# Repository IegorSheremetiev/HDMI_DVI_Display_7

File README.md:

### HDMI/DVI to LVDS(OLDI) Converter
These days we may find many electronic devices what are to old already or where the "white smoke" gone.
But could be that the display module is still alive!
Excatly this story started when my old and really weak netbook Acer A-150 just stopped working. There is no sense to try to restore it. Howevere there are several interesting modules inside. An I inspired to do something intersting with that parts.

First of all the idea of the current project is to realize its display module as the second tiny (7") disaply for the local PC.
Or, to get portable display for headless PCs. Time to time even for these machines the display is requried.
And later I found in my "almost trash boxes" the old tablet where HW is pretty old but the display and the touchscreen are really fine. Bu this is another story

## System definition and key components
As the input signal I chose TMDS based signals: DVI and HDMI. IN almost all cases these two standards are similar. HDMI has bonuses as it may include audio stream. ANd this idea I would like to realize. However market checks showed the lack of components with HDMI Audio support in stock. Nevertheless, if the HDMI doesn't inlcude Audio Stream DVI and HDMI are fully compatible.

Analog Interface (D-Sub) is fully feasible. However it old. Could be later but not now.

Key Components:
- [TFP401A](https://www.ti.com/product/TFP401A) - TMDS to RGB24 decoder; translate DV/HDMI digital signals to paraller RGB 8:8:8 interface, the device has ODD and EVEN outputs what gives to it ability to handle high resolutions
- [SN65LVDS93A](https://www.ti.com/product/SN65LVDS93A) - RGB24 to LVDS converter; serialize RGB signals into the LVDS interface (or OpenLDI) interface; different configurations of connections gives the possibility to use different color resolution of displays RGB12/RGB18/RGB24
- [TPS54286 or TPS54283](https://www.ti.com/lit/gpn/tps54283) - Dual DC-DC Converter for the system;
  - 3V3 as the main power supply for the system
  - 5V as the power supply for the backlight
- [AUO B089AW01-V1](https://datasheetspdf.com/pdf-file/1304972/AUO/B089AW01-V1/1) - the display module used in my broken netbook

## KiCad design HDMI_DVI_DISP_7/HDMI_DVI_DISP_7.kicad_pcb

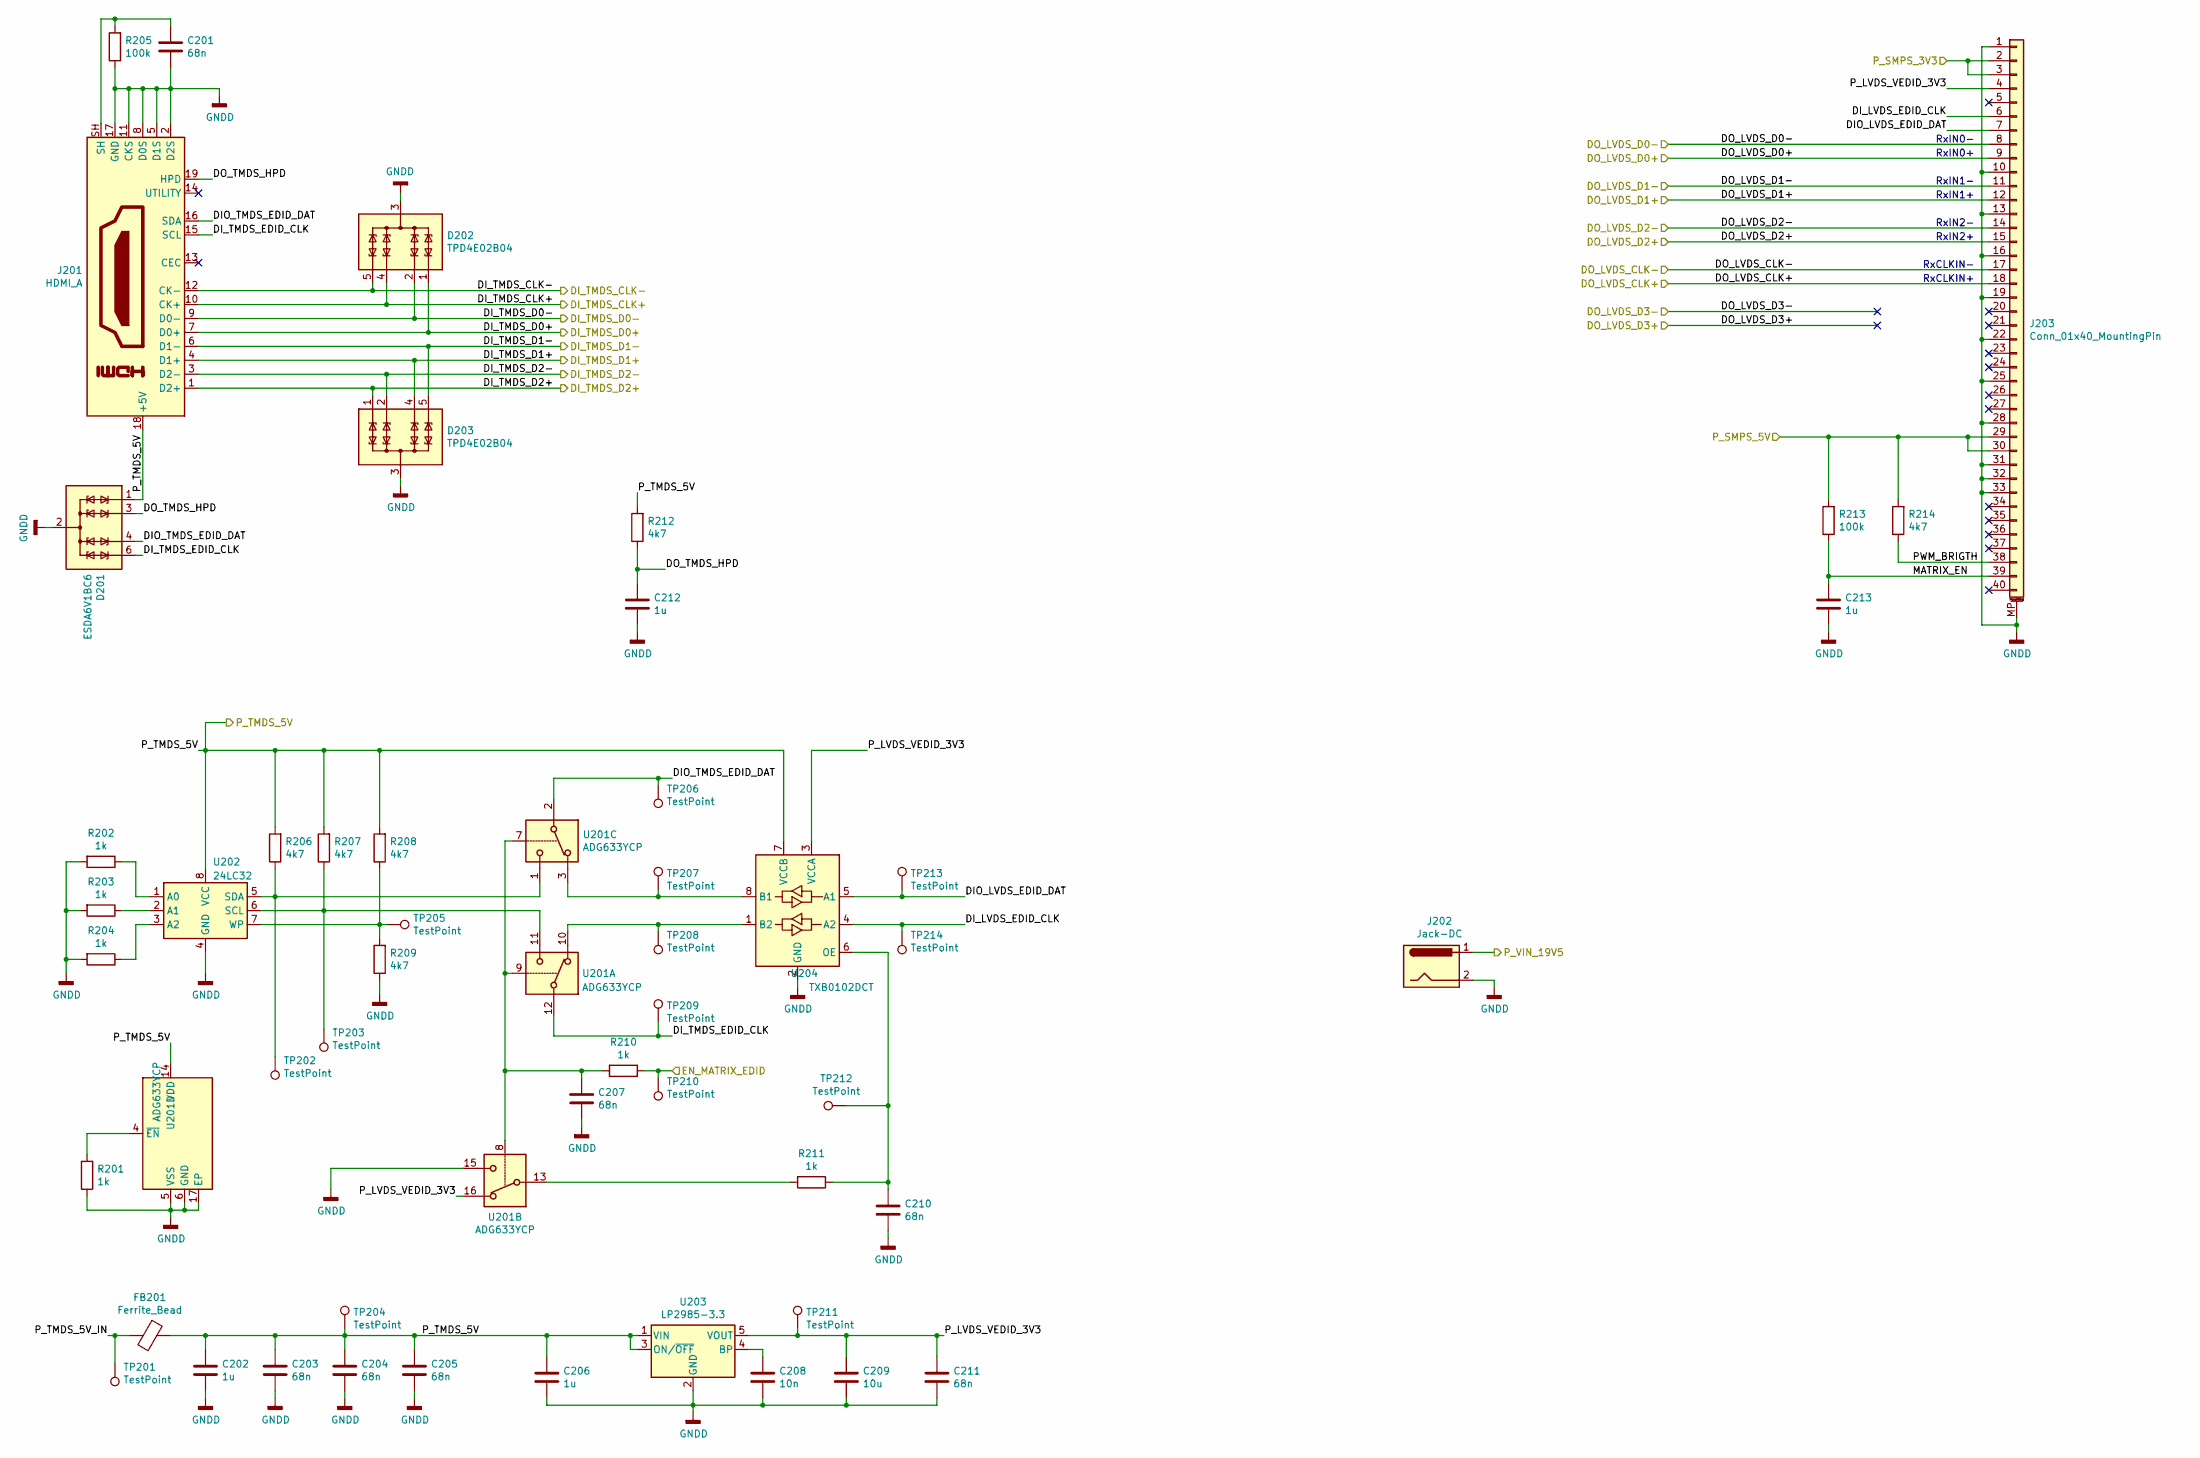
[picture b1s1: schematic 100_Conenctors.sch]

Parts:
C201, C203, C204, C205, C207, C210, C211: 68n; C_0402_1005Metric
C202, C206: 1u; C_0603_1608Metric
C208: 10n; C_0402_1005Metric
C209: 10u; C_0805_2012Metric
C212, C213: 1u; C_0402_1005Metric
D201: ESDA6V1BC6; SOT-23-6
D202, D203: TPD4E02B04; USON-10_-_1mm_x_2.5mm_x_0.55mm
FB201: Ferrite_Bead; L_0603_1608Metric
J201: HDMI_A; HDMI_A_19p_0.5mm
J202: Jack-DC; PinHeader_1x02_P1.27mm_Horizontal
J203: Conn_01x40_MountingPin; Hirose_FH12-40S-0.5SH_1x40-1MP_P0.50mm_Horizontal
R201, R202, R203, R204, R210, R211: 1k; R_0402_1005Metric
R205, R213: 100k; R_0402_1005Metric
R206, R207, R208, R209, R212, R214: 4k7; R_0402_1005Metric
TP201, TP202, TP203, TP204, TP205, TP206, TP207, TP208, TP209, TP210, TP211, TP212, TP213, TP214: TestPoint; TestPoint_Pad_D1.0mm
U201: ADG633YCP; LFCSP-16-1EP_4x4mm_P0.65mm_EP2.1x2.1mm
U202: 24LC32; SOIC-8_3.9x4.9mm_P1.27mm
U203: LP2985-3.3; SOT-23-5
U204: TXB0102DCT; TSSOP-8_3x3mm_P0.65mm

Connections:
/100_Conenctors/DIO_LVDS_EDID_DAT: J203.7, TP213.1, U204.5 (A1)
/100_Conenctors/DIO_TMDS_EDID_DAT: D201.4 (TVS3), J201.16 (SDA), TP206.1, U201.2
/100_Conenctors/DI_LVDS_EDID_CLK: J203.6, TP214.1, U204.4 (A2)
/100_Conenctors/DI_TMDS_CLK+: D202.4 (IO3), D202.7 (NC), J201.10 (CK+); also elsewhere on the board
/100_Conenctors/DI_TMDS_CLK-: D202.5 (IO4), D202.6 (NC), J201.12 (CK-); also elsewhere on the board
/100_Conenctors/DI_TMDS_D0+: D202.1 (IO1), D202.10 (NC), J201.7 (D0+); also elsewhere on the board
/100_Conenctors/DI_TMDS_D0-: D202.2 (IO2), D202.9 (NC), J201.9 (D0-); also elsewhere on the board
/100_Conenctors/DI_TMDS_D1+: D203.4 (IO3), D203.7 (NC), J201.4 (D1+); also elsewhere on the board
/100_Conenctors/DI_TMDS_D1-: D203.5 (IO4), D203.6 (NC), J201.6 (D1-); also elsewhere on the board
/100_Conenctors/DI_TMDS_D2+: D203.1 (IO1), D203.10 (NC), J201.1 (D2+); also elsewhere on the board
/100_Conenctors/DI_TMDS_D2-: D203.2 (IO2), D203.9 (NC), J201.3 (D2-); also elsewhere on the board
/100_Conenctors/DI_TMDS_EDID_CLK: D201.6 (TVS4), J201.15 (SCL), TP209.1, U201.12
/100_Conenctors/DO_LVDS_CLK+: J203.18; also elsewhere on the board
/100_Conenctors/DO_LVDS_CLK-: J203.17; also elsewhere on the board
/100_Conenctors/DO_LVDS_D0+: J203.9; also elsewhere on the board
/100_Conenctors/DO_LVDS_D0-: J203.8; also elsewhere on the board
/100_Conenctors/DO_LVDS_D1+: J203.12; also elsewhere on the board
/100_Conenctors/DO_LVDS_D1-: J203.11; also elsewhere on the board
/100_Conenctors/DO_LVDS_D2+: J203.15; also elsewhere on the board
/100_Conenctors/DO_LVDS_D2-: J203.14; also elsewhere on the board
/100_Conenctors/DO_TMDS_HPD: C212.1, D201.3 (TVS2), J201.19 (HPD), R212.1
/100_Conenctors/MATRIX_EN: C213.1, J203.39, R213.1
/100_Conenctors/PWM_BRIGTH: J203.38, R214.1
/100_Conenctors/P_LVDS_VEDID_3V3: C209.1, C211.1, J203.4, TP211.1, U201.16, U203.5 (VOUT), U204.3 (VCCA)
/100_Conenctors/P_TMDS_5V_IN: FB201.2, TP201.1
/900_Video_Links/DO_LVDS_EDID: R210.1, TP210.1; also elsewhere on the board
/P_SMPS_3V3: J203.2, J203.3; also elsewhere on the board
/P_SMPS_5V: J203.29, J203.30, R213.2, R214.2; also elsewhere on the board
/P_TMDS_5V: C202.1, C203.1, C204.1, C205.1, C206.1, D201.1 (TVS1), FB201.1, J201.18 (+5V), R206.2, R207.2, R208.2, R212.2, TP204.1, U201.14 (VDD), U202.8 (VCC), U203.1 (VIN), U203.3 (ON/~OFF~), U204.7 (VCCB); also elsewhere on the board
/P_VIN_19V5: J202.1; also elsewhere on the board
GNDD: C201.2, C202.2, C203.2, C204.2, C205.2, C206.2, C207.2, C208.2, C209.2, C210.2, C211.2, C212.2, C213.2, D201.2 (COM), D201.5 (COM), D202.3 (GND), D202.8 (GND), D203.3 (GND), D203.8 (GND), J201.2 (D2S), J201.5 (D1S), J201.8 (D0S), J201.11 (CKS), J201.17 (GND), J202.2, J203.1, J203.10, J203.13, J203.16, J203.19, J203.22, J203.25, J203.28, J203.31, J203.32, J203.33, J203.MP (MountPin), R201.1, R202.2, R203.2, R204.2, R205.1, R209.1, U201.5 (VSS), U201.6 (GND), U201.15, U201.17 (EP), U202.4 (GND), U203.2 (GND), U204.2 (GND); also elsewhere on the board
unnamed: C201.1, J201.SH, R205.2
unnamed: C207.1, R210.2, U201.7, U201.8, U201.9
unnamed: C208.1, U203.4 (BP)
unnamed: C210.1, R211.1, TP212.1, U204.6 (OE)
unnamed: R201.2, U201.4 (~EN)
unnamed: R202.1, U202.1 (A0)
unnamed: R203.1, U202.2 (A1)
unnamed: R204.1, U202.3 (A2)
unnamed: R206.1, TP202.1, U201.1, U202.5 (SDA)
unnamed: R207.1, TP203.1, U201.11, U202.6 (SCL)
unnamed: R208.1, R209.2, TP205.1, U202.7 (WP)
unnamed: R211.2, U201.13
unnamed: TP207.1, U201.3, U204.8 (B1)
unnamed: TP208.1, U201.10, U204.1 (B2)

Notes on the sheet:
RxIN0-
RxIN0+
RxIN1-
RxIN1+
RxIN2-
RxIN2+
RxCLKIN-
RxCLKIN+

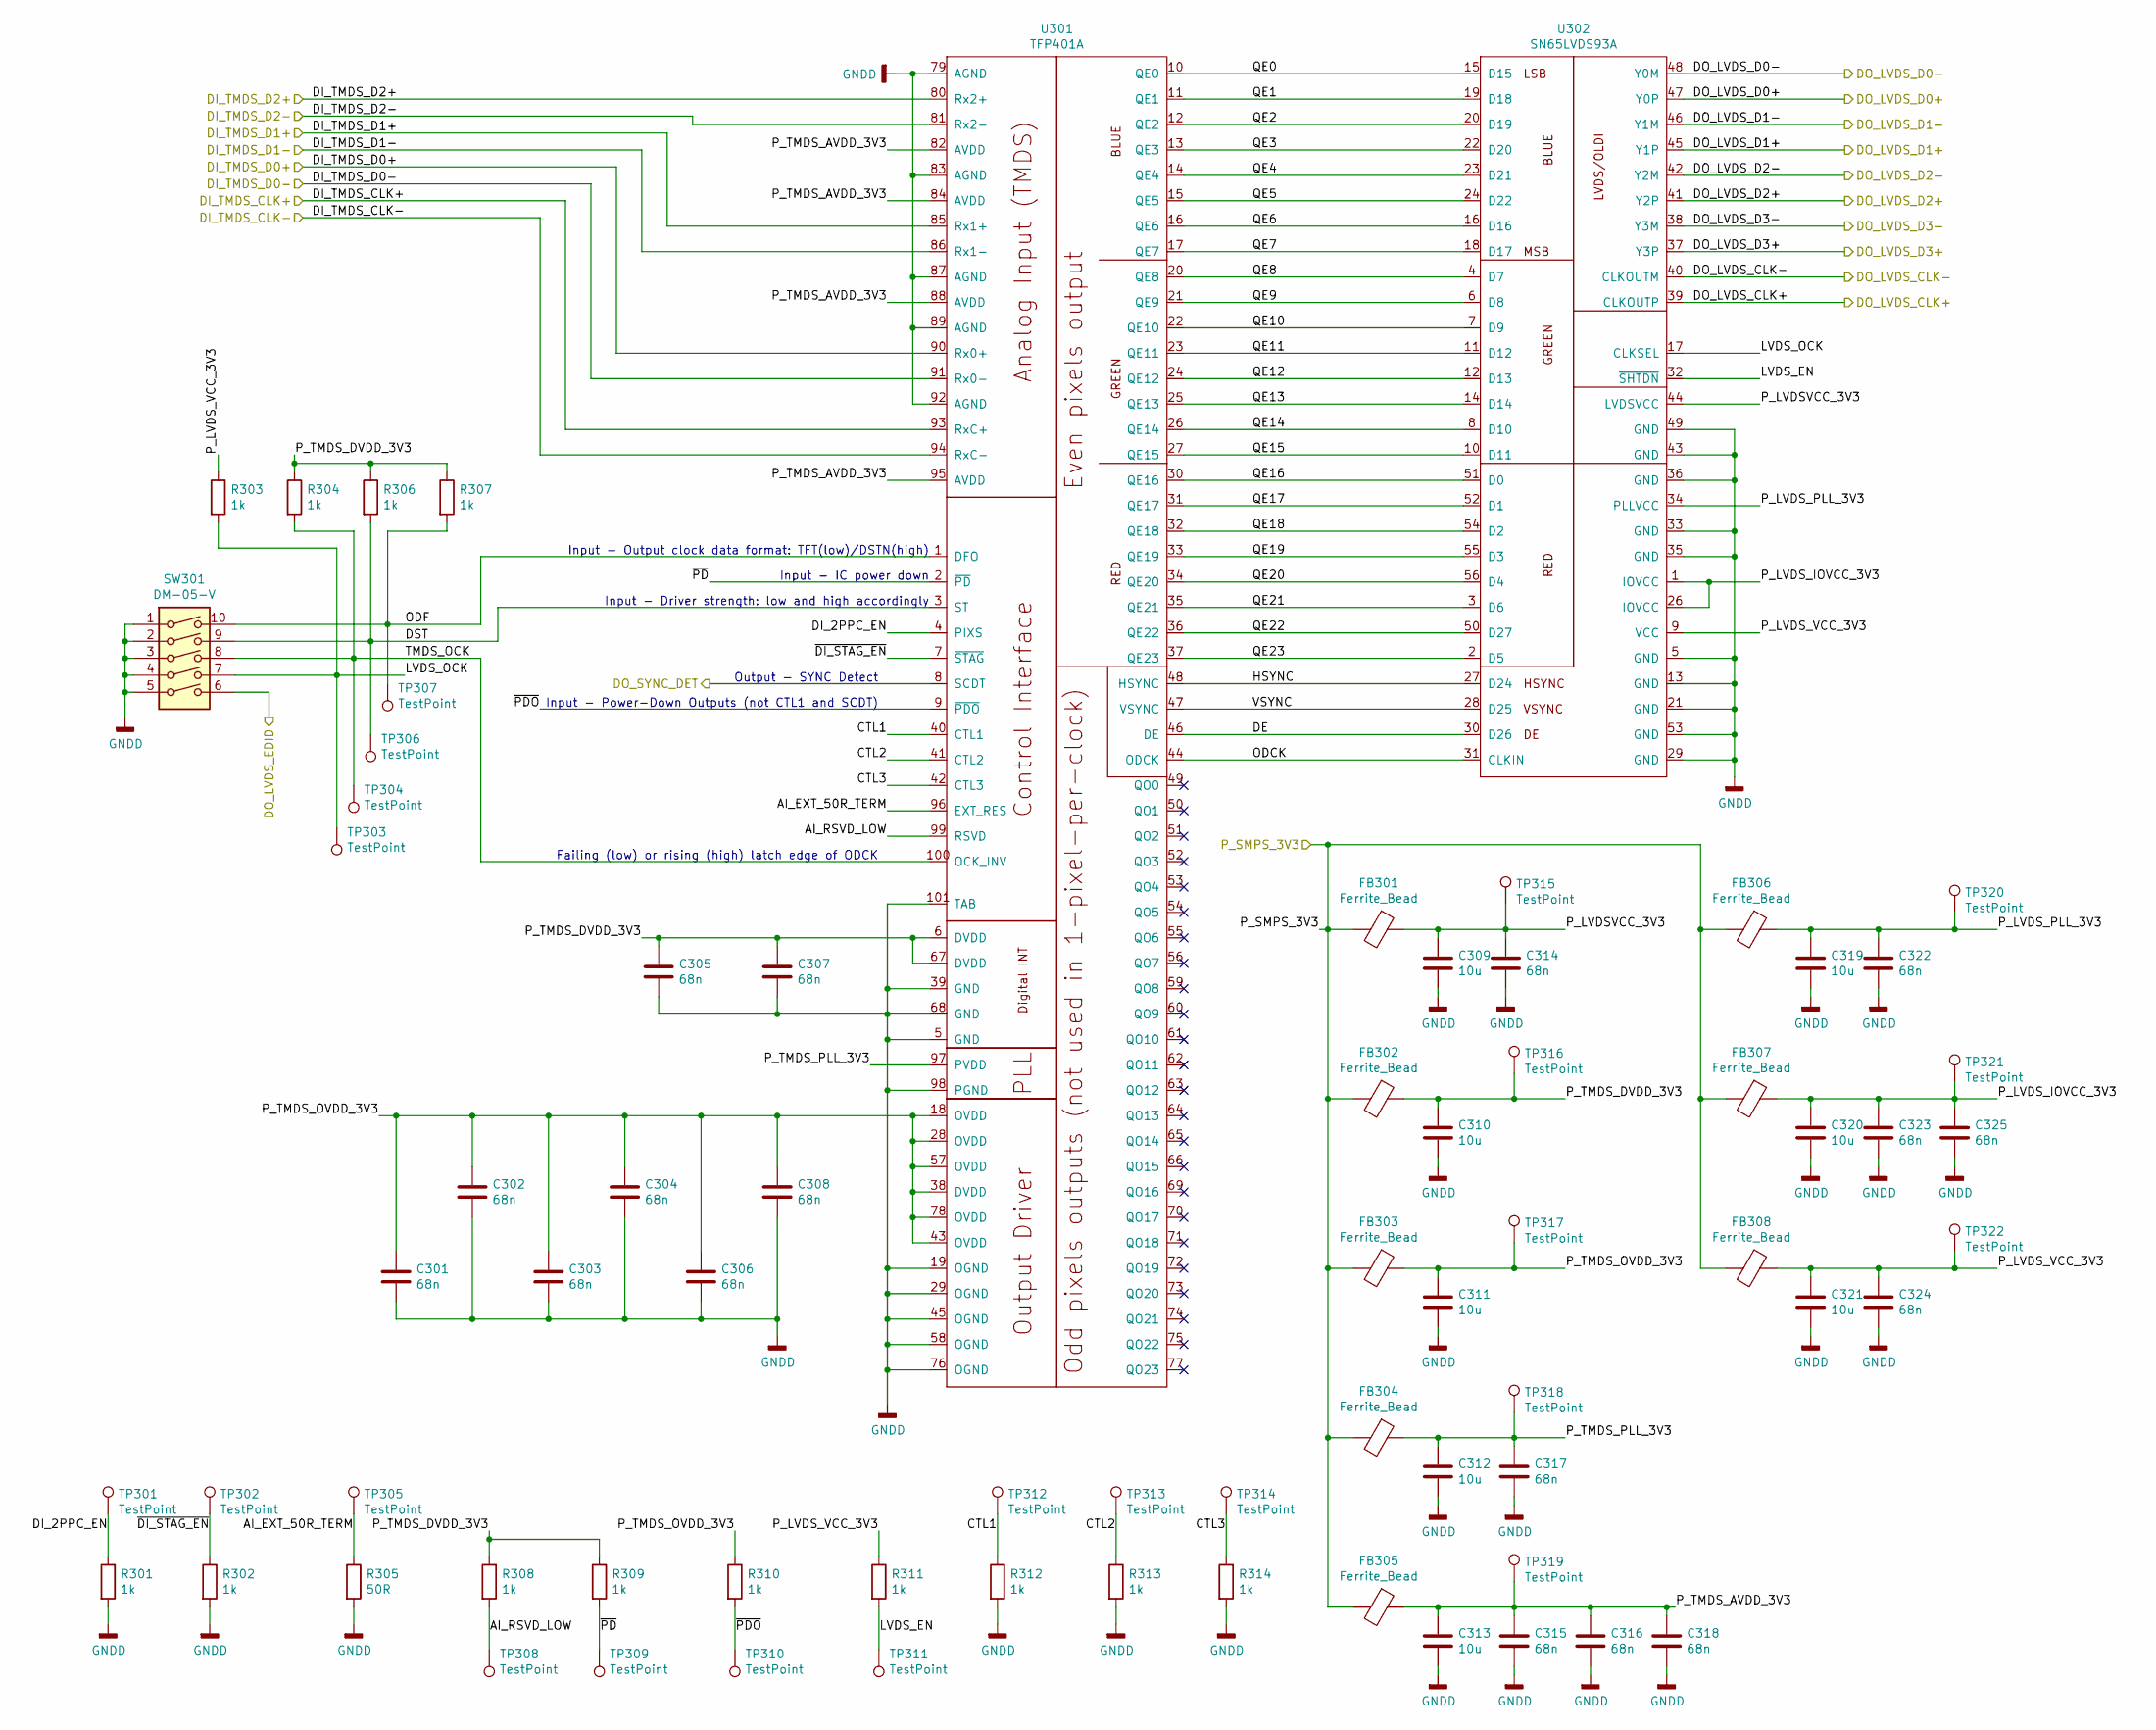
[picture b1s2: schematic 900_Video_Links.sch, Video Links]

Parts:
C301, C302, C303, C304, C305, C306, C307, C308, C314, C315, C316, C317, C318, C322, C323, C324, C325: 68n; C_0402_1005Metric
C309, C310, C311, C312, C313, C319, C320, C321: 10u; C_0805_2012Metric
FB301, FB302, FB303, FB304, FB305, FB306, FB307, FB308: Ferrite_Bead; L_0603_1608Metric
R301, R302, R303, R304, R306, R307, R308, R309, R310, R311, R312, R313, R314: 1k; R_0402_1005Metric
R305: 50R; R_0402_1005Metric
SW301: DM-05-V; SOIC-10-DM-05
TP301, TP302, TP303, TP304, TP305, TP306, TP307, TP308, TP309, TP310, TP311, TP312, TP313, TP314, TP315, TP316, TP317, TP318, TP319, TP320, TP321, TP322: TestPoint; TestPoint_Pad_D1.0mm
U301: TFP401A; TQFP-100-1EP_14x14mm_P0.5mm_EP5x5mm_ThermalVias
U302: SN65LVDS93A; TSSOP-56_6.1x14mm_P0.5mm

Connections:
/100_Conenctors/DI_TMDS_CLK+: U301.93 (RxC+); also elsewhere on the board
/100_Conenctors/DI_TMDS_CLK-: U301.94 (RxC-); also elsewhere on the board
/100_Conenctors/DI_TMDS_D0+: U301.90 (Rx0+); also elsewhere on the board
/100_Conenctors/DI_TMDS_D0-: U301.91 (Rx0-); also elsewhere on the board
/100_Conenctors/DI_TMDS_D1+: U301.85 (Rx1+); also elsewhere on the board
/100_Conenctors/DI_TMDS_D1-: U301.86 (Rx1-); also elsewhere on the board
/100_Conenctors/DI_TMDS_D2+: U301.80 (Rx2+); also elsewhere on the board
/100_Conenctors/DI_TMDS_D2-: U301.81 (Rx2-); also elsewhere on the board
/100_Conenctors/DO_LVDS_CLK+: U302.39 (CLKOUTP); also elsewhere on the board
/100_Conenctors/DO_LVDS_CLK-: U302.40 (CLKOUTM); also elsewhere on the board
/100_Conenctors/DO_LVDS_D0+: U302.47 (Y0P); also elsewhere on the board
/100_Conenctors/DO_LVDS_D0-: U302.48 (Y0M); also elsewhere on the board
/100_Conenctors/DO_LVDS_D1+: U302.45 (Y1P); also elsewhere on the board
/100_Conenctors/DO_LVDS_D1-: U302.46 (Y1M); also elsewhere on the board
/100_Conenctors/DO_LVDS_D2+: U302.41 (Y2P); also elsewhere on the board
/100_Conenctors/DO_LVDS_D2-: U302.42 (Y2M); also elsewhere on the board
/900_Video_Links/AI_EXT_50R_TERM: R305.1, TP305.1, U301.96 (EXT_RES)
/900_Video_Links/AI_RSVD_LOW: R308.2, TP308.1, U301.99 (RSVD)
/900_Video_Links/CTL1: R312.1, TP312.1, U301.40 (CTL1)
/900_Video_Links/CTL2: R313.1, TP313.1, U301.41 (CTL2)
/900_Video_Links/CTL3: R314.1, TP314.1, U301.42 (CTL3)
/900_Video_Links/DE: U301.46 (DE), U302.30 (D26)
/900_Video_Links/DI_2PPC_EN: R301.1, TP301.1, U301.4 (PIXS)
/900_Video_Links/DO_LVDS_EDID: SW301.6; also elsewhere on the board
/900_Video_Links/DST: R306.2, SW301.9, TP306.1, U301.3 (ST)
/900_Video_Links/HSYNC: U301.48 (HSYNC), U302.27 (D24)
/900_Video_Links/LVDS_EN: R311.2, TP311.1, U302.32 (~SHTDN)
/900_Video_Links/LVDS_OCK: R303.2, SW301.7, TP303.1, U302.17 (CLKSEL)
/900_Video_Links/ODCK: U301.44 (ODCK), U302.31 (CLKIN)
/900_Video_Links/ODF: R307.2, SW301.10, TP307.1, U301.1 (DFO)
/900_Video_Links/P_LVDSVCC_3V3: C309.1, C314.1, FB301.1, TP315.1, U302.44 (LVDSVCC)
/900_Video_Links/P_LVDS_IOVCC_3V3: C320.1, C323.1, C325.1, FB307.1, TP321.1, U302.1 (IOVCC), U302.26 (IOVCC)
/900_Video_Links/P_LVDS_PLL_3V3: C319.1, C322.1, FB306.1, TP320.1, U302.34 (PLLVCC)
/900_Video_Links/P_LVDS_VCC_3V3: C321.1, C324.1, FB308.1, R303.1, R311.1, TP322.1, U302.9 (VCC)
/900_Video_Links/P_TMDS_AVDD_3V3: C313.1, C315.1, C316.1, C318.1, FB305.1, TP319.1, U301.82 (AVDD), U301.84 (AVDD), U301.88 (AVDD), U301.95 (AVDD)
/900_Video_Links/P_TMDS_DVDD_3V3: C305.1, C307.1, C310.1, FB302.1, R304.1, R306.1, R307.1, R308.1, R309.1, TP316.1, U301.6 (DVDD), U301.67 (DVDD)
/900_Video_Links/P_TMDS_OVDD_3V3: C301.1, C302.1, C303.1, C304.1, C306.1, C308.1, C311.1, FB303.1, R310.1, TP317.1, U301.18 (OVDD), U301.28 (OVDD), U301.38 (DVDD), U301.43 (OVDD), U301.57 (OVDD), U301.78 (OVDD)
/900_Video_Links/P_TMDS_PLL_3V3: C312.1, C317.1, FB304.1, TP318.1, U301.97 (PVDD)
/900_Video_Links/QE0: U301.10 (QE0), U302.15 (D15)
/900_Video_Links/QE1: U301.11 (QE1), U302.19 (D18)
/900_Video_Links/QE2: U301.12 (QE2), U302.20 (D19)
/900_Video_Links/QE3: U301.13 (QE3), U302.22 (D20)
/900_Video_Links/QE4: U301.14 (QE4), U302.23 (D21)
/900_Video_Links/QE5: U301.15 (QE5), U302.24 (D22)
/900_Video_Links/QE6: U301.16 (QE6), U302.16 (D16)
/900_Video_Links/QE7: U301.17 (QE7), U302.18 (D17)
/900_Video_Links/QE8: U301.20 (QE8), U302.4 (D7)
/900_Video_Links/QE9: U301.21 (QE9), U302.6 (D8)
/900_Video_Links/QE10: U301.22 (QE10), U302.7 (D9)
/900_Video_Links/QE11: U301.23 (QE11), U302.11 (D12)
/900_Video_Links/QE12: U301.24 (QE12), U302.12 (D13)
/900_Video_Links/QE13: U301.25 (QE13), U302.14 (D14)
/900_Video_Links/QE14: U301.26 (QE14), U302.8 (D10)
/900_Video_Links/QE15: U301.27 (QE15), U302.10 (D11)
/900_Video_Links/QE16: U301.30 (QE16), U302.51 (D0)
/900_Video_Links/QE17: U301.31 (QE17), U302.52 (D1)
/900_Video_Links/QE18: U301.32 (QE18), U302.54 (D2)
/900_Video_Links/QE19: U301.33 (QE19), U302.55 (D3)
/900_Video_Links/QE20: U301.34 (QE20), U302.56 (D4)
/900_Video_Links/QE21: U301.35 (QE21), U302.3 (D6)
/900_Video_Links/QE22: U301.36 (QE22), U302.50 (D27)
/900_Video_Links/QE23: U301.37 (QE23), U302.2 (D5)
/900_Video_Links/TMDS_OCK: R304.2, SW301.8, TP304.1, U301.100 (OCK_INV)
/900_Video_Links/VSYNC: U301.47 (VSYNC), U302.28 (D25)
/900_Video_Links/~DI_STAG_EN: R302.1, TP302.1, U301.7 (~STAG)
/900_Video_Links/~PD: R309.2, TP309.1, U301.2 (~PD)
/900_Video_Links/~PDO: R310.2, TP310.1, U301.9 (~PDO)
/DO_SYNC_DET: U301.8 (SCDT); also elsewhere on the board
/P_SMPS_3V3: FB301.2, FB302.2, FB303.2, FB304.2, FB305.2, FB306.2, FB307.2, FB308.2; also elsewhere on the board
GNDD: C301.2, C302.2, C303.2, C304.2, C305.2, C306.2, C307.2, C308.2, C309.2, C310.2, C311.2, C312.2, C313.2, C314.2, C315.2, C316.2, C317.2, C318.2, C319.2, C320.2, C321.2, C322.2, C323.2, C324.2, C325.2, R301.2, R302.2, R305.2, R312.2, R313.2, R314.2, SW301.1, SW301.2, SW301.3, SW301.4, SW301.5, U301.5 (GND), U301.19 (OGND), U301.29 (OGND), U301.39 (GND), U301.45 (OGND), U301.58 (OGND), U301.68 (GND), U301.76 (OGND), U301.79 (AGND), U301.83 (AGND), U301.87 (AGND), U301.89 (AGND), U301.92 (AGND), U301.98 (PGND), U301.101 (TAB), U302.5 (GND), U302.13 (GND), U302.21 (GND), U302.29 (GND), U302.33 (GND), U302.35 (GND), U302.36 (GND), U302.43 (GND), U302.49 (GND), U302.53 (GND); also elsewhere on the board

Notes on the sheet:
Input - Power-Down Outputs (not CTL1 and SCDT)
Input - Driver strength: low and high accordingly
Failing (low) or rising (high) latch edge of ODCK
Input - IC power down
Output - SYNC Detect
Input - Output clock data format: TFT(low)/DSTN(high)

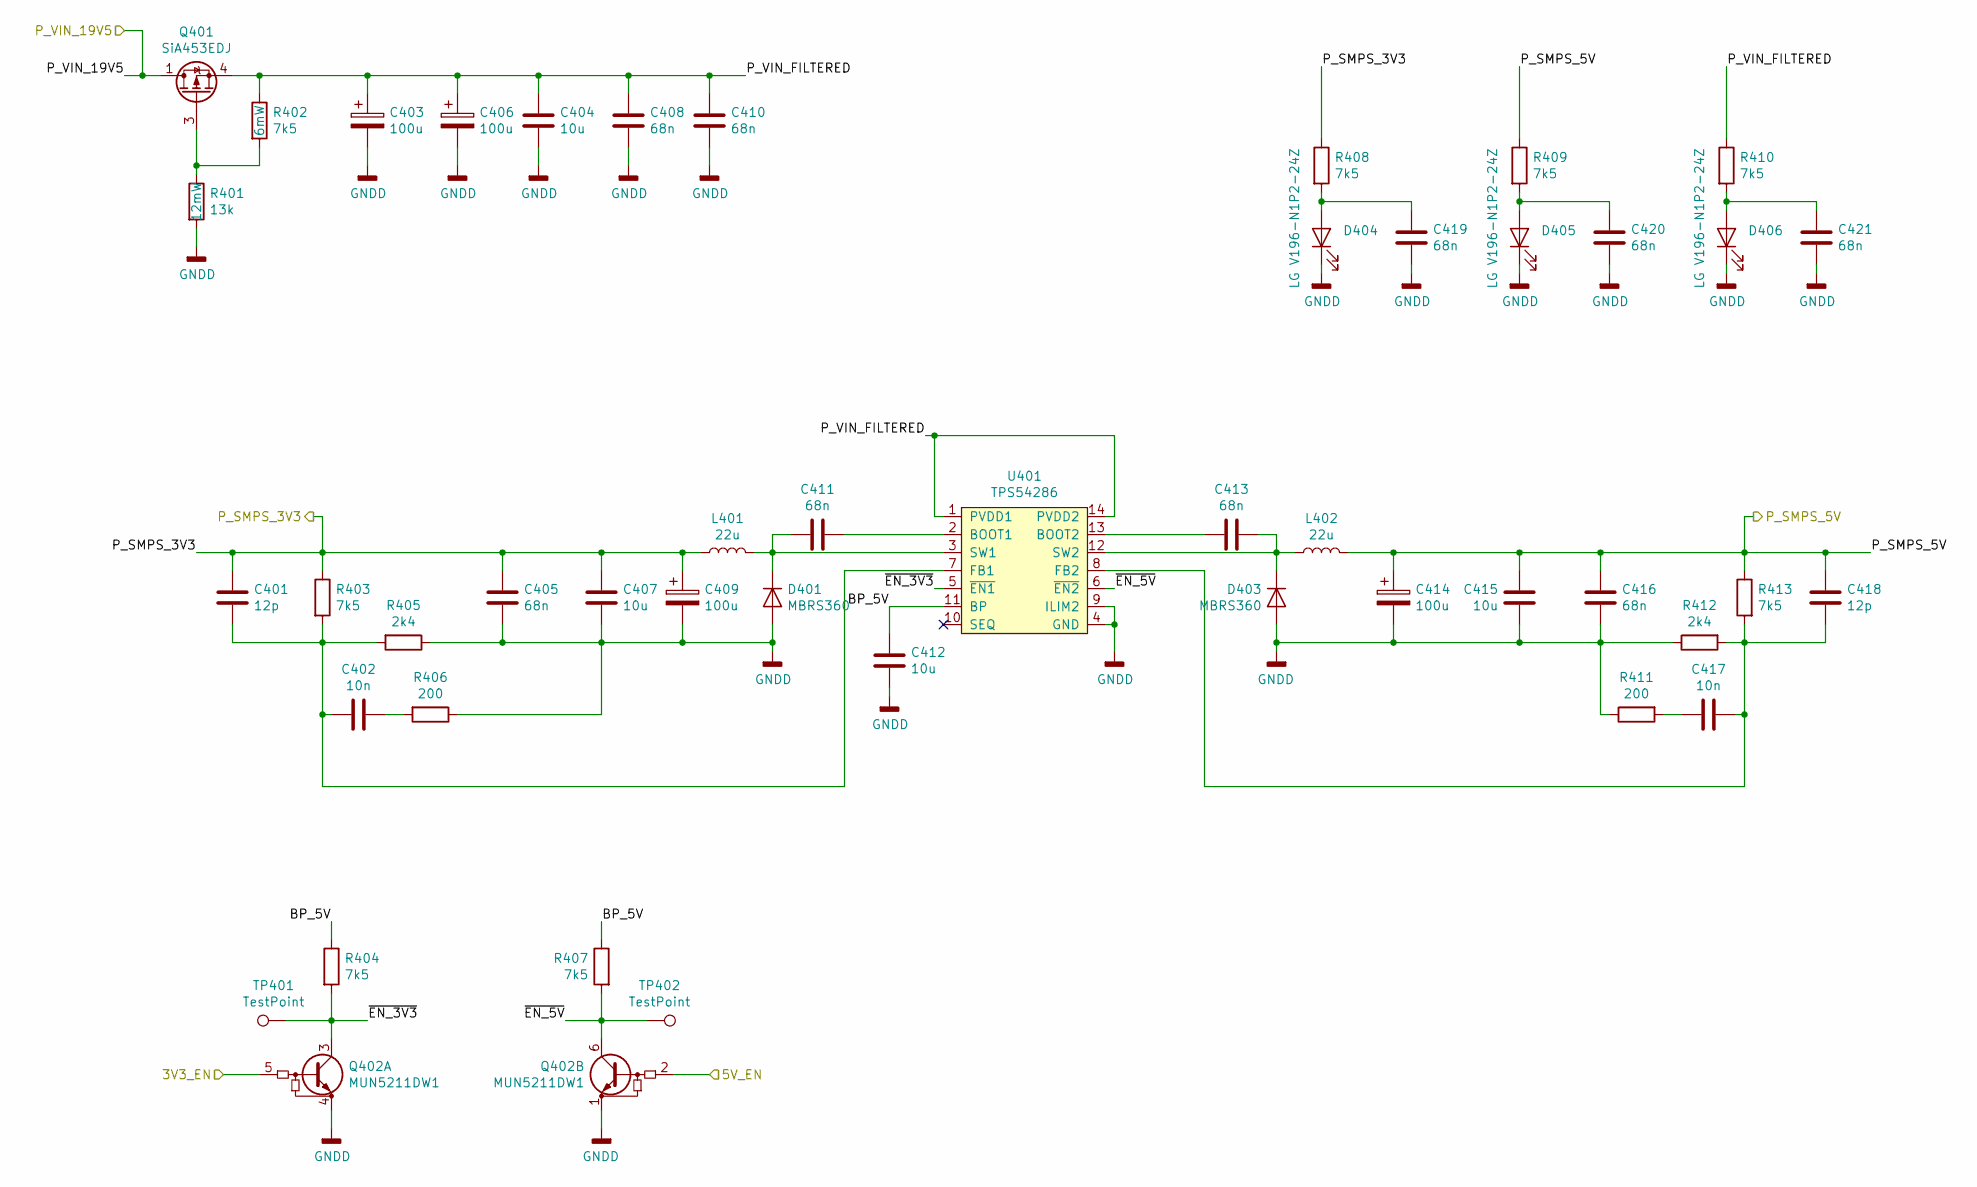
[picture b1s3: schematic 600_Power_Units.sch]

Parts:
C401, C418: 12p; C_0402_1005Metric
C402, C417: 10n; C_0402_1005Metric
C403, C406, C409, C414: 100u; CP_Elec_8x10
C404: 10u; C_0603_1608Metric
C405, C408, C410, C411, C413, C416, C419, C420, C421: 68n; C_0402_1005Metric
C407, C412, C415: 10u; C_0805_2012Metric
D401, D403: MBRS360; D_SMC
D404, D405, D406: LG V196-N1P2-24Z; OSRAM_LED_1x1x1.8
L401, L402: 22u; IND_12065
Q401: SiA453EDJ; Vishay_PowerPAK_SC70-6L_Single
Q402: MUN5211DW1; SOT-363_SC-70-6
R401: 13k; R_0402_1005Metric
R402, R403, R404, R407, R408, R409, R410, R413: 7k5; R_0402_1005Metric
R405, R412: 2k4; R_0402_1005Metric
R406, R411: 200; R_0402_1005Metric
TP401, TP402: TestPoint; TestPoint_Pad_D1.0mm
U401: TPS54286; HTSSOP-5.0x4.4-14x0.65-EP

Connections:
/600_Power_Units/BP_5V: C412.1, R404.1, R407.1, U401.11 (BP)
/600_Power_Units/P_VIN_FILTERED: C403.1, C404.1, C406.1, C408.1, C410.1, Q401.4 (S), R402.1, R410.1, U401.1 (PVDD1), U401.14 (PVDD2)
/600_Power_Units/~EN_3V3: Q402.3 (C1), R404.2, TP401.1, U401.5 (~EN1)
/600_Power_Units/~EN_5V: Q402.6 (C1), R407.2, TP402.1, U401.6 (~EN2)
/DO_SYNC_DET: Q402.2 (B1); also elsewhere on the board
/P_SMPS_3V3: C401.1, C405.1, C407.1, C409.1, L401.1, R403.1, R408.1; also elsewhere on the board
/P_SMPS_5V: C414.1, C415.1, C416.1, C418.1, L402.1, R409.1, R413.1; also elsewhere on the board
/P_TMDS_5V: Q402.5 (B1); also elsewhere on the board
/P_VIN_19V5: Q401.1 (D); also elsewhere on the board
GNDD: C403.2, C404.2, C405.2, C406.2, C407.2, C408.2, C409.2, C410.2, C412.2, C414.2, C415.2, C416.2, C419.2, C420.2, C421.2, D401.2 (A), D403.2 (A), D404.1 (K), D405.1 (K), D406.1 (K), Q402.1 (E1), Q402.4 (E1), R401.2, R405.1, R406.1, R411.1, R412.1, U401.4 (GND), U401.9 (ILIM2), U401.15 (TAB); also elsewhere on the board
unnamed: C401.2, C402.2, R403.2, R405.2, U401.7 (FB1)
unnamed: C402.1, R406.2
unnamed: C411.1, U401.2 (BOOT1)
unnamed: C411.2, D401.1 (K), L401.2, U401.3 (SW1)
unnamed: C413.1, U401.13 (BOOT2)
unnamed: C413.2, D403.1 (K), L402.2, U401.12 (SW2)
unnamed: C417.1, C418.2, R412.2, R413.2, U401.8 (FB2)
unnamed: C417.2, R411.2
unnamed: C419.1, D404.2 (A), R408.2
unnamed: C420.1, D405.2 (A), R409.2
unnamed: C421.1, D406.2 (A), R410.2
unnamed: Q401.3 (G), R401.1, R402.2

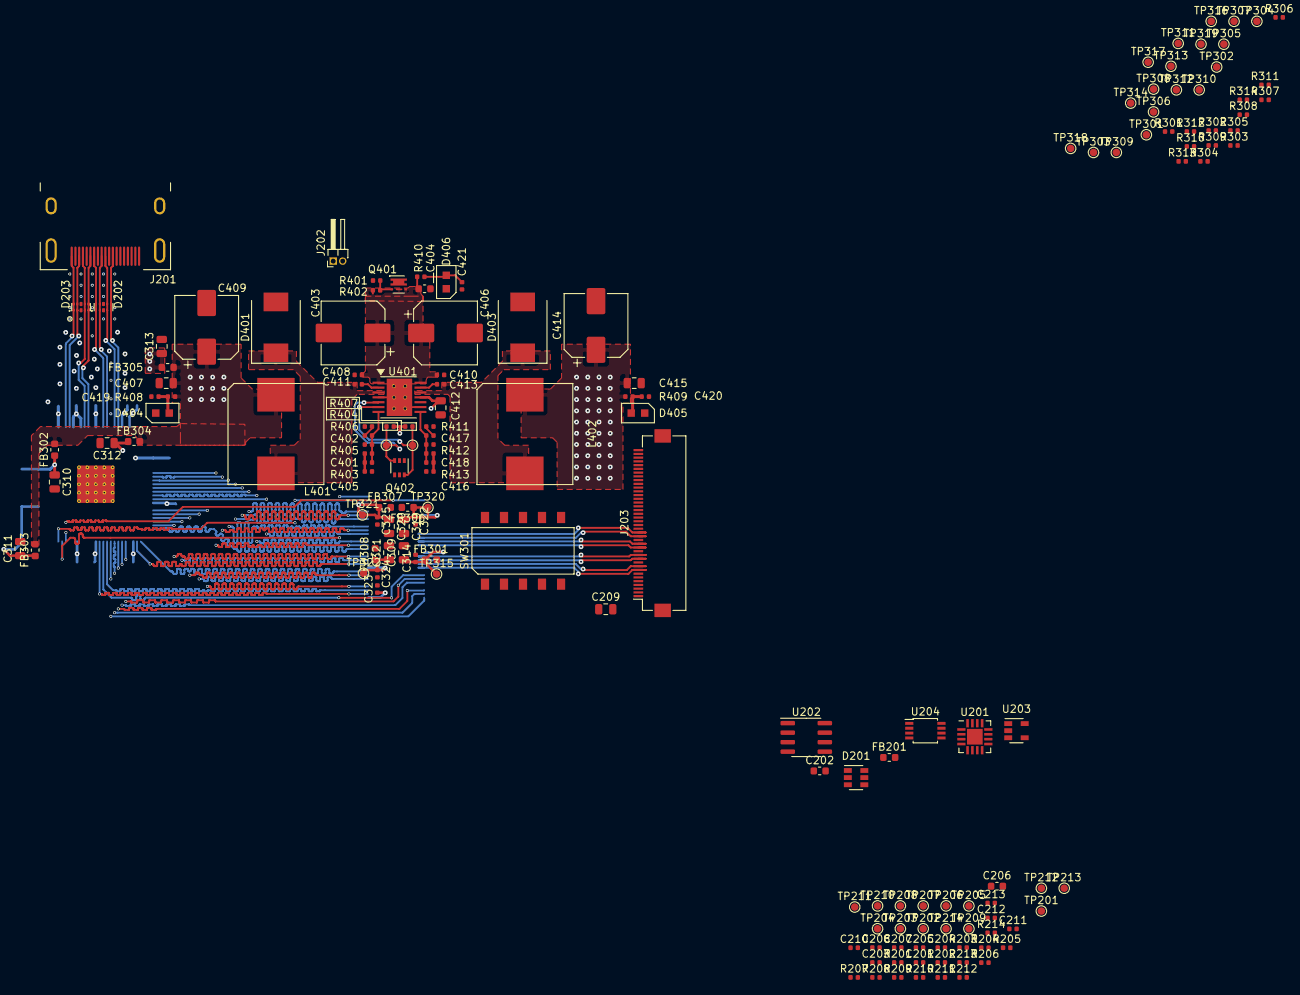
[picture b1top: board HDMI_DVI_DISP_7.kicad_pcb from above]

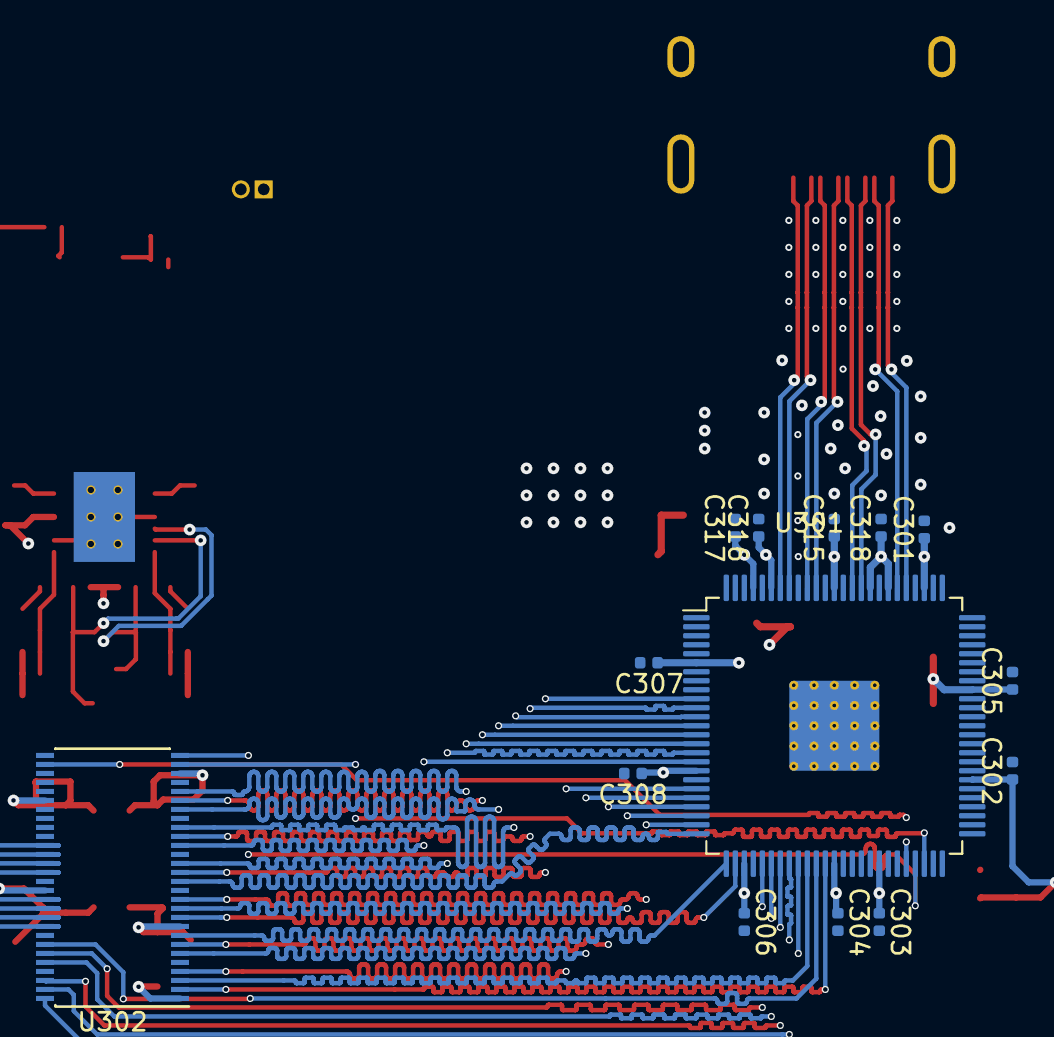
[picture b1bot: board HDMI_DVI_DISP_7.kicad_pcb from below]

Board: 4 copper layers, 170 parts (14 on the bottom side), 112 nets.

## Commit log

2021-04-21 Initial Release Pure schematic is done, mostly for training purposes
2021-04-21 README.md file added. Prepare to push to server
2021-04-21 .gitignore file added
2021-04-21 README.md filled with details actual for 21-Apr-2021
2021-04-22 The base structure defined for PS
2021-04-24 Daily job done
2021-04-26 Cleanup
2021-04-26 All packages are added
2021-04-28 Packages are done. Only few are missing. Layout started
2021-04-30 PS Layout done
2021-05-11 Major progress of PCB layout
